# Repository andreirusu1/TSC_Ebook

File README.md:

# TSC_Ebook
Descriere Proiect
OpenBook este un proiect open source care isi propune sa creeze un e-book reader accesibil si usor de produs. Dispozitivul este conceput pentru a afisa carti digitale, oferind o experienta de lectura similara cu cea a unei carti tiparite, dar cu avantajele tehnologiei moderne. Proiectul meu se bazeaza pe o proiectare simpla si eficienta, iar in aceasta etapa s-au dezvoltat schema electronica, PCB-ul si plasarea componentelor pe placa.

Pentru a transforma aceasta viziune in realitate, am parcurs urmatoarele etape:

1)Engineering Validation (EVT): Am proiectat schema electronica si am creat PCB-ul, asigurandu-ne ca fiecare conexiune este optimizata pentru performanta si fiabilitate.

2)Modelare 3D: Am verificat plasarea componentelor pe placa intr-un mediu 3D, garantand ca designul se integreaza perfect in cadrul final al dispozitivului.

3)Partea de display, baterie si modelele 3D complete ale dispozitivului nu au fost dezvoltate inca. Acest repository se concentreaza pe proiectarea schematica, realizarea PCB-ului si plasarea componentelor pe placa in mediul 3D.

Diagrama Bloc

Mai jos se prezinta o diagrama bloc schematica a principalelor componente si a interconexiunilor acestora:

Bill Of Materials (BOM)
Nr.	Componenta	Datasheet URL	Link site pt procurare

1	ESP32-C6-WROOM-1-N8	[Datasheet](https://www.espressif.com/sites/default/files/documentation/esp32-c6-wroom-1_wroom-1u_datasheet_en.pdf)	[link](https://www.digikey.com/en/products/detail/espressif-systems/ESP32-C6-WROOM-1-N8/17728866?utm_source=snapeda&utm_campaign=buynow&utm_medium=aggregator)

2	Micro-SD	[Datasheet](https://www.attend.com.tw/data/download/file/112A-TAAR-R03_Spec.pdf)	[link](https://www.digikey.com/en/products/detail/attend-technology/112A-TAAR-R03/17633923)

3	Inductor (68µH)	[Datasheet](https://www.we-online.com/components/products/datasheet/784373170680.pdf)	[link](https://ro.mouser.com/ProductDetail/Wurth-Elektronik/784373170680?qs=sGAEpiMZZMv126LJFLh8yzGkpireax1GgDeN9GF1EUQ%3D)

4	LED	[Datasheet](https://www.bridgelux.com/sites/default/files/resource_media/DS51_Rev%20F%20Bridgelux%20SMD%203030%20Data%20sheet.pdf)	[link](https://www.digikey.com/en/products/detail/bridgelux/BXEM-27E0000-0-000/6618599)

5	Buttons	[Datasheet](https://configured-product-images.s3.amazonaws.com/Datasheets/TL3315.pdf)	[link](https://www.digikey.com/en/products/detail/e-switch/TL3315NF250Q/1870396)

6	Capacitor 	[Datasheet](https://eu.mouser.com/datasheet/2/40/cx5r_KGM-3223198.pdf)	[link](https://ro.mouser.com/ProductDetail/KYOCERA-AVX/0402YD104MAT2A?qs=4PckX6MNpMErOINbbZj3Cw%3D%3D&srsltid=AfmBOorRllqAGFDVGSlUxRe1HCu5DEMiSSNplU-KeE2woDnCuT1J4_ia)

7	Rezistori	[Datasheet](https://www.yageo.com/upload/media/product/products/datasheet/rchip/PYu-RC_Group_51_RoHS_L_12.pdf)	[link](https://www.digikey.com/en/products/detail/yageo/RC0402JR-07100KL/726416)

8	Diode (Schottky Rectifier)	[Datasheet](https://datasheets.kyocera-avx.com/schottky.pdf)	[link](https://www.digikey.com/en/products/detail/kyocera-avx/sd0805s020s1r0/3749517)

9	Connector USB (Type-C)	[Datasheet](https://gct.co/files/drawings/usb4110.pdf)	[Mouser](https://ro.mouser.com/ProductDetail/GCT/USB4110-GF-A?qs=KUoIvG%2F9IlYiZvIXQjyJeA%3D%3D&utm_id=6470900573&utm_source=google&utm_medium=cpc&utm_marketing_tactic=emeacorp&gad_source=1)

10	Test Pad 	[DataSheet](https://cdn-shop.adafruit.com/product-files/3825/3825_diagram.PDF) [link](https://componentsearchengine.com/prices/3825?manufacturer=Adafruit)

 Aceasta lista este orientativa. Componentele si specificatiile pot fi ajustate pe parcursul dezvoltarii.

Functionalitatea Hardware
Proiectul se bazeaza pe microcontroller-ul ESP32-C6, iar designul hardware a fost gandit pentru a optimiza functionalitatea si integrarea componentelor. Principalele aspecte includ:

Alimentare: Dispozitivul este alimentat printr-un regulator de tensiune care transforma 5V in 3.3V, necesar pentru functionarea corecta a ESP32-C6.

Conectivitate: ESP32-C6 pune la dispozitie mai multe interfete de comunicatie (UART, SPI, I2C), esentiale pentru conectarea senzorilor si a altor periferice.

Plasare Componentelor: Schematicul si PCB-ul au fost proiectate pentru a asigura o dispunere eficienta a componentelor, reducand interferentele electromagnetice si facilitand asamblarea manuala sau automatizata.

Verificare 3D: Modelul 3D realizat in Fusion360 (exportat ca .step) a fost folosit pentru a verifica plasarea corecta a componentelor pe placa.

Configurarea Pinilor ESP32-C6
Mai jos sunt detaliate functiile pinilor utilizati in proiect:

Pin	    Functie	          Descriere
GPIO1	  TX	            Transmiterea datelor catre periferice

GPIO3	  RX	            Receptionarea datelor de la periferice

GPIO12	I2C             SDA	Linie de date pentru comunicatia I2C

GPIO13	I2C             SCL	Linie de ceas pentru comunicatia I2C

GPIO14	Buton/Resetare	Functie de resetare a dispozitivului

Configuratia pinilor poate fi ajustata.

Planuri de Dezvoltare: Etapele urmatoare includ integrarea componentelor pentru display, alimentare prin baterie si dezvoltarea completa a modelului 3D al dispozitivului pentru validarea finala.

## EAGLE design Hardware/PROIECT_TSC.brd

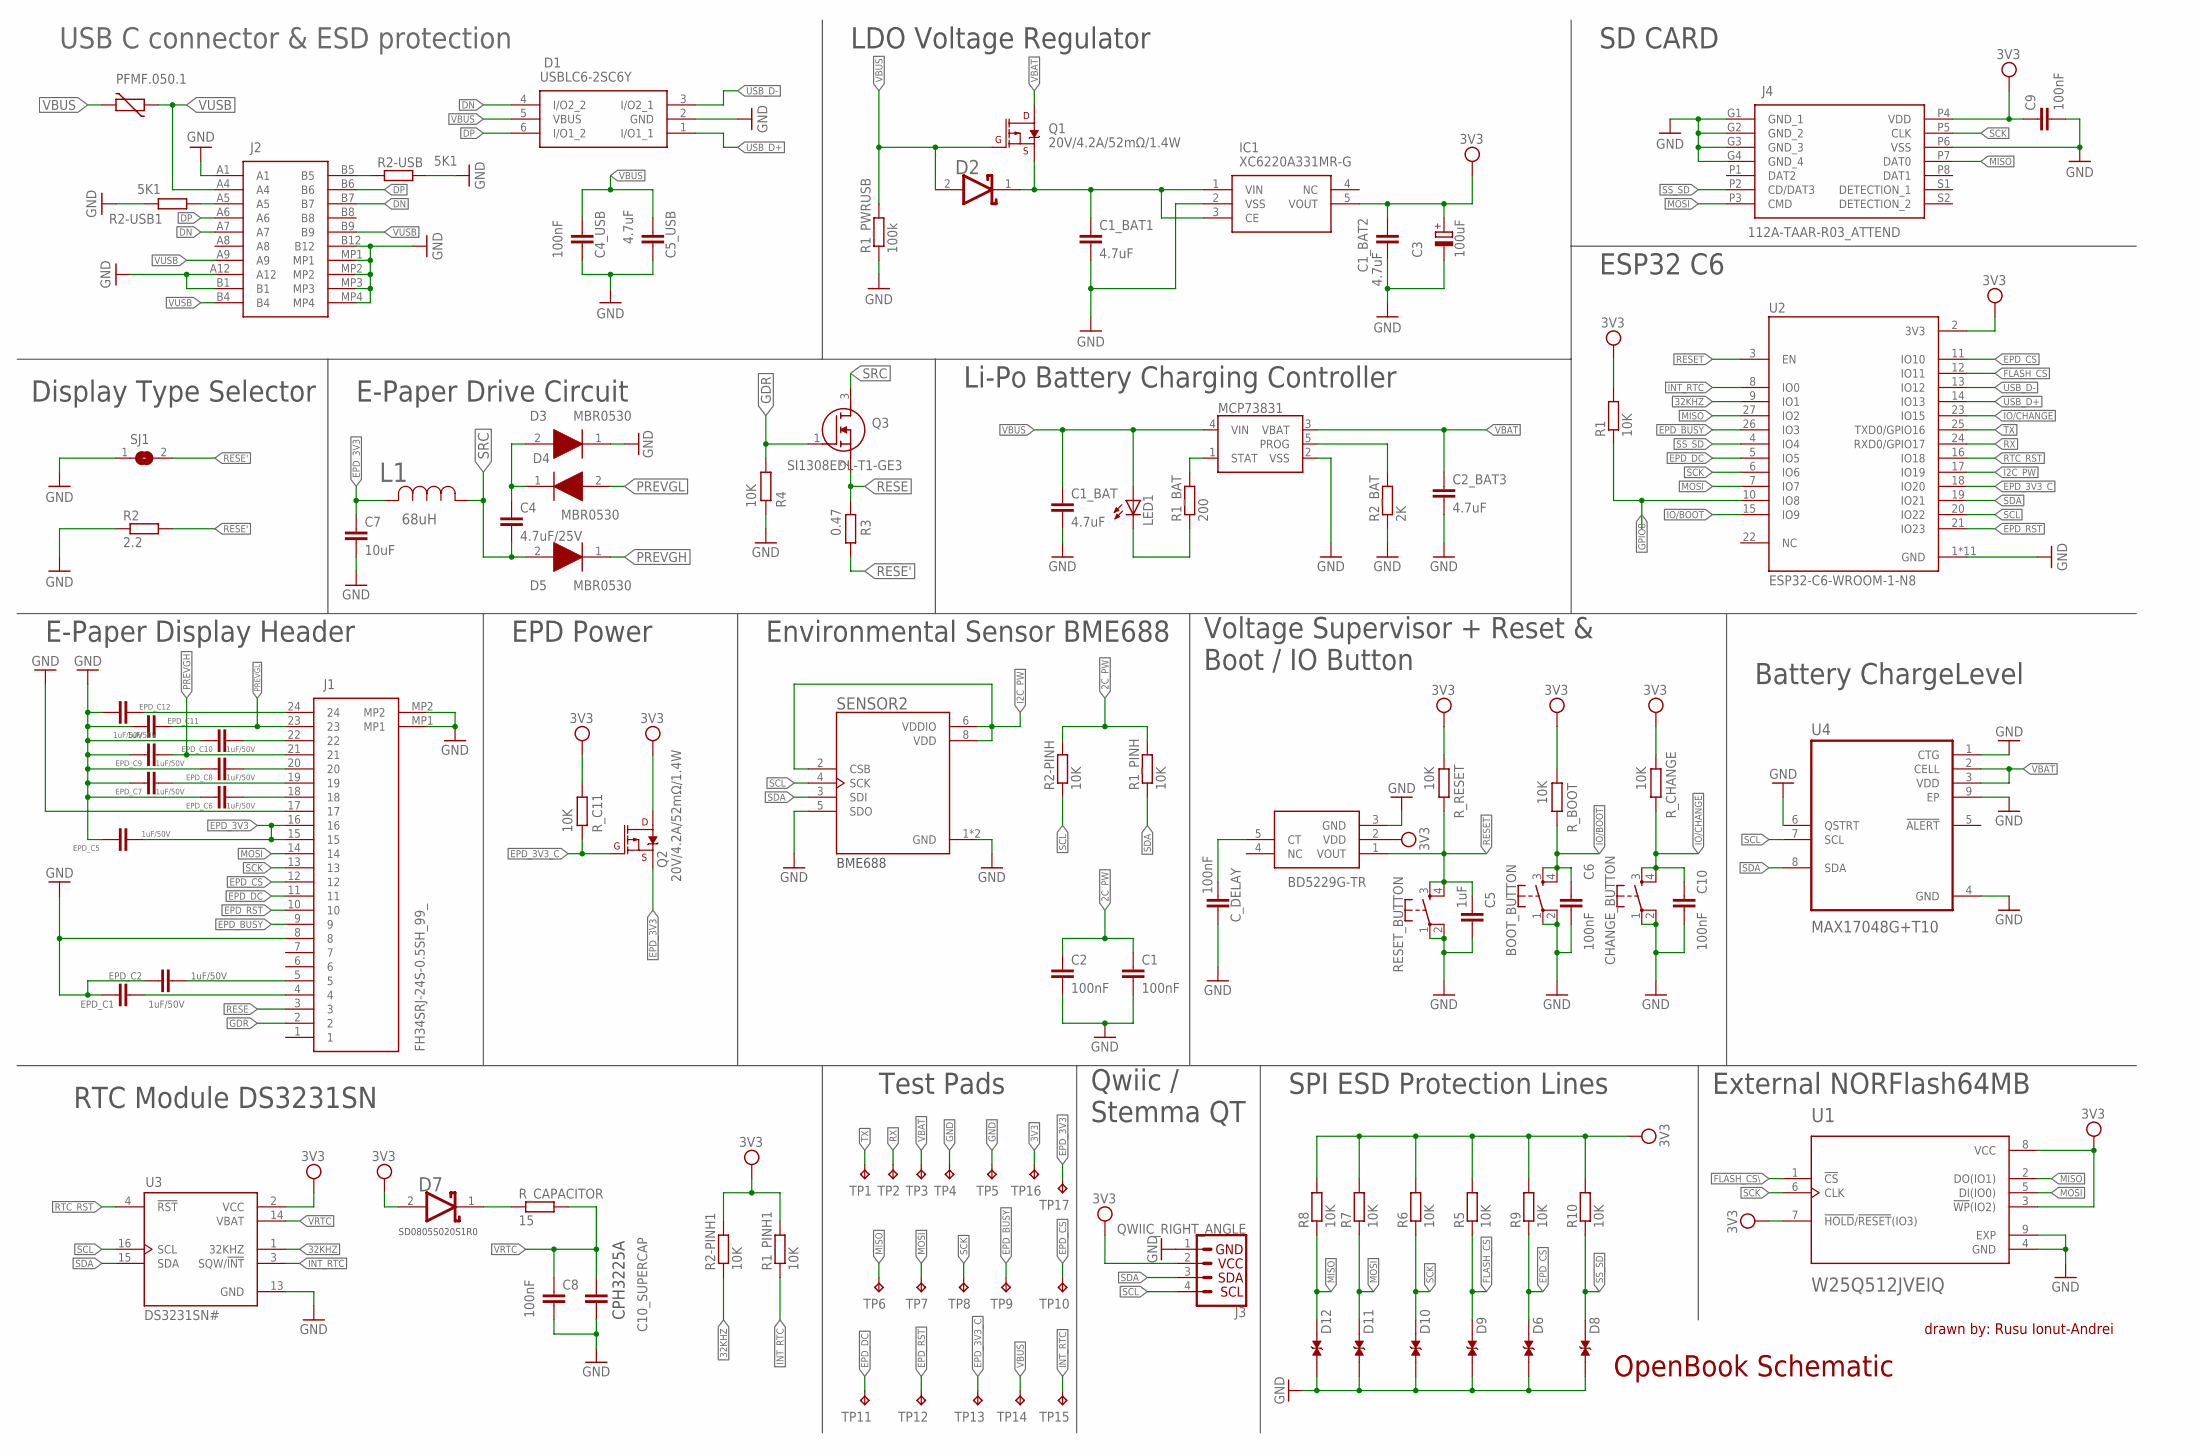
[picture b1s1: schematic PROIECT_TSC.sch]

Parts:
BOOT_BUTTON: BUTTON_CUSYOMV1; MYBUTTON
C1, C2, C6, C8, C9, C10: 100nF; ESP32_WROVER_EAGLE-LTSPICE_C0402
C1_BAT, C1_BAT1, C2_BAT3: 4.7uF; ESP32_WROVER_EAGLE-LTSPICE_C0402
C1_BAT2, C5_USB: 4.7uF; EAGLE-LTSPICE_C0402
C3: 100uF; RCL_CT3528
C4: 4.7uF/25V; ESP32_WROVER_EAGLE-LTSPICE_C0402
C4_USB: 100nF; EAGLE-LTSPICE_C0402
C5: 1uF; ESP32_WROVER_EAGLE-LTSPICE_C0402
C7: 10uF; EAGLE-LTSPICE_C0402
C10_SUPERCAP: ESP32_WROVER_EAGLE-LTSPICE_CC0402; ESP32_WROVER_EAGLE-LTSPICE_C0402
CHANGE_BUTTON: BUTTON_CUSYOMV1; MYBUTTON
C_DELAY: 100nF; ESP32_WROVER_EAGLE-LTSPICE_C0402
D1: USBLC6-2SC6Y; SOT95P280X145-6N
D2, D7: ESP32_WROVER_AVX---SD0805S020S1R0_AVX_SD0805S020S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; ESP32_WROVER_AVX---SD0805S020S1R0_AVX_SD0805S020S1R0_0
D3, D4, D5: MBR0530; SOD3716X135N
D6, D8, D9, D10, D11, D12: PGB1010603MR; DIOC1608X36N
EPD_C1, EPD_C2, EPD_C5, EPD_C6, EPD_C7, EPD_C8, EPD_C9, EPD_C10, EPD_C11, EPD_C12: 1uF/50V; ESP32_WROVER_EAGLE-LTSPICE_C0402
IC1: XC6220A331MR-G; SOT95P280X120-5N
IC2: BD5229G-TR; SOT95P280X125-5N
J1: FH34SRJ-24S-0.5SH_99_; FH34SRJ24S05SH99
J2: SAMACSYS_PARTS_USB4110-GF-A; SAMACSYS_PARTS_USB4110GFA
J3: QWIIC_RIGHT_ANGLE; JST04_1MM_RA
J4: 112A-TAAR-R03_ATTEND; 112ATAARR03ATTEND
L1: 68uH; IND_4828-WE-TPC_WRE
LED1: ADAFRUIT_LEDCHIP-LED0603; ADAFRUIT_CHIP-LED0603
MCP73831: ESP32_WROVER_SPARKFUN-IC-POWER_MCP73831; ESP32_WROVER_SPARKFUN-IC-POWER_SOT23-5
PFMF.050.1: ESP32C6_VARISTORCN1812; ESP32C6_VARISTOR_CT/CN1812
Q1, Q2: 20V/4.2A/52mΩ/1.4W; ESP32_WROVER_SPARKFUN-DISCRETESEMI_SOT23-3
Q3: SI1308EDL-T1-GE3; SOT65P210X110-3N
R1, R1_PINH, R1_PINH1, R2-PINH, R2-PINH1, R4, R5, R6, R7, R8, R9, R10: 10K; ESP32_WROVER_EAGLE-LTSPICE_R0402
R1_BAT: 200; ESP32_WROVER_EAGLE-LTSPICE_R0402
R1_PWRUSB: 100k; ESP32_WROVER_EAGLE-LTSPICE_R0402
R2: 2.2; ESP32_WROVER_EAGLE-LTSPICE_R0402
R2-USB, R2-USB1: 5K1; ESP32_WROVER_EAGLE-LTSPICE_R0402
R2_BAT: 2K; ESP32_WROVER_EAGLE-LTSPICE_R0402
R3: 0.47; ESP32_WROVER_EAGLE-LTSPICE_R0402
RESET_BUTTON: BUTTON_CUSYOMV1; MYBUTTON
R_BOOT: 10K; ESP32_WROVER_EAGLE-LTSPICE_R0402
R_C11: 10K; ESP32_WROVER_EAGLE-LTSPICE_R0402
R_CAPACITOR: 15; ESP32_WROVER_EAGLE-LTSPICE_R0402
R_CHANGE: 10K; ESP32_WROVER_EAGLE-LTSPICE_R0402
R_RESET: 10K; ESP32_WROVER_EAGLE-LTSPICE_R0402
SENSOR2: ESP32_WROVER_BME680_BME680; ESP32_WROVER_BME680_PSON80P300X300X100-8N
SJ1: SJ
TP1, TP2, TP3, TP4, TP5, TP6, TP7, TP8, TP9, TP10, TP11, TP12, TP13, TP14, TP15, TP16, TP17: TPTP20R; TP20R
U1: W25Q512JVEIQ; SON127P600X800X80-9N
U2: ESP32-C6-WROOM-1-N8; XCVR_ESP32-C6-WROOM-1-N8
U3: DS3231SN#; SOIC127P1032X265-16N
U4: MAX17048G+T10; SON50P200X200X80-9N

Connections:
2C_PW: C1.1, C2.1, R1_PINH.2, R2-PINH.2
3V3: C1_BAT2.1, C3.+, C9.1, D7.2 (ANODE), IC1.5 (VOUT), IC2.2 (VDD), J3.2, J4.P4 (VDD), Q2.3 (D), R1.2, R1_PINH1.2, R2-PINH1.2, R5.2, R6.2, R7.2, R8.2, R9.2, R10.2, R_BOOT.2, R_C11.2, R_CHANGE.2, R_RESET.2, TP16.TP, U1.3 (!WP!(IO2)), U1.7 (!HOLD!/!RESET!(IO3)), U1.8 (VCC), U2.2 (3V3), U3.2 (VCC)
32KHZ: R2-PINH1.1, U2.9 (IO1), U3.1 (32KHZ)
DN: D1.4 (I/O2_2), J2.A7, J2.B7
DP: D1.6 (I/O1_2), J2.A6, J2.B6
EPD_3V3: C7.1, EPD_C5.2, J1.15, J1.16, L1.2, Q2.2 (S), TP17.TP
EPD_3V3_C: Q2.1 (G), R_C11.1, TP13.TP, U2.18 (IO20)
EPD_BUSY: J1.9, TP9.TP, U2.26 (IO3)
EPD_CS: D6.2, J1.12, R9.1, TP10.TP, U2.11 (IO10)
EPD_DC: J1.11, TP11.TP, U2.5 (IO5)
EPD_RST: J1.10, TP12.TP, U2.21 (IO23)
FLASH_CS: D9.2, R5.1, U2.12 (IO11)
FLASH_CS\: U1.1 (!CS)
GDR: J1.2, Q3.1 (G), R4.2
GND: BOOT_BUTTON.1, BOOT_BUTTON.2, C1.2, C1_BAT.2, C1_BAT1.2, C1_BAT2.2, C2.2, C2_BAT3.2, C3.-, C4_USB.2, C5.2, C5_USB.2, C6.2, C7.2, C8.2, C9.2, C10.2, C10_SUPERCAP.2, CHANGE_BUTTON.1, CHANGE_BUTTON.2, C_DELAY.2, D1.2 (GND), D3.1 (K), D6.1, D8.1, D9.1, D10.1, D11.1, D12.1, EPD_C1.1, EPD_C2.1, EPD_C5.1, EPD_C6.1, EPD_C7.1, EPD_C8.1, EPD_C9.1, EPD_C10.1, EPD_C11.1, EPD_C12.1, IC1.2 (VSS), IC2.3 (GND), J1.8, J1.17, J1.MP1, J1.MP2, J2.A1, J2.A12, J2.B1, J2.B12, J2.MP1, J2.MP2, J2.MP3, J2.MP4, J3.1, J4.G1 (GND_1), J4.G2 (GND_2), J4.G3 (GND_3), J4.G4 (GND_4), J4.P6 (VSS), MCP73831.2 (VSS), R1_PWRUSB.1, R2.1, R2-USB.2, R2-USB1.1, R2_BAT.1, R4.1, RESET_BUTTON.1, RESET_BUTTON.2, SENSOR2.1 (GND), SENSOR2.5 (SDO), SENSOR2.7 (GND), SJ1.1, TP4.TP, TP5.TP, U1.4 (GND), U1.9 (EXP), U2.1 (GND), U2.28 (GND), U2.29_1 (GND), U2.29_2 (GND), U2.29_3 (GND), U2.29_4 (GND), U2.29_5 (GND), U2.29_6 (GND), U2.29_7 (GND), U2.29_8 (GND), U2.29_9 (GND), U3.13 (GND), U4.1 (CTG), U4.4 (GND), U4.6 (QSTRT), U4.9 (EP)
GPIO8: R1.1, U2.10 (IO8)
I2C_PW: SENSOR2.2 (CSB), SENSOR2.6 (VDDIO), SENSOR2.8 (VDD), U2.17 (IO19)
INT_RTC: R1_PINH1.1, TP15.TP, U2.8 (IO0), U3.3 (SQW/!INT)
IO/BOOT: BOOT_BUTTON.3, BOOT_BUTTON.4, C6.1, R_BOOT.1, U2.15 (IO9)
IO/CHANGE: C10.1, CHANGE_BUTTON.3, CHANGE_BUTTON.4, R_CHANGE.1, U2.23 (IO15)
MISO: D12.2, J4.P7 (DAT0), R8.1, TP6.TP, U1.2 (DO(IO1)), U2.27 (IO2)
MOSI: D11.2, J1.14, J4.P3 (CMD), R7.1, TP7.TP, U1.5 (DI(IO0)), U2.7 (IO7)
unnamed: C1_BAT1.1, D2.1 (CATHODE), IC1.1 (VIN), IC1.3 (CE), Q1.2 (S)
unnamed: J2.A5, R2-USB1.2
unnamed: C4.1, D3.2 (A), D4.1 (K)
unnamed: J2.B5, R2-USB.1
unnamed: MCP73831.1 (STAT), R1_BAT.2
unnamed: MCP73831.5 (PROG), R2_BAT.2
unnamed: LED1.C, R1_BAT.1
unnamed: EPD_C12.2, J1.24
unnamed: EPD_C2.2, J1.5
unnamed: EPD_C1.2, J1.4
unnamed: EPD_C6.2, J1.18
unnamed: EPD_C10.2, J1.22
unnamed: EPD_C8.2, J1.20
unnamed: D7.1 (CATHODE), R_CAPACITOR.1
unnamed: EPD_C7.2, J1.19
unnamed: C_DELAY.1, IC2.5 (CT)
PREVGH: D5.1 (K), EPD_C9.2, J1.21
PREVGL: D4.2 (A), EPD_C11.2, J1.23
RESE: J1.3, Q3.2 (S), R3.2
RESE': R2.2, R3.1, SJ1.2
RESET: C5.1, IC2.1 (VOUT), RESET_BUTTON.3, RESET_BUTTON.4, R_RESET.1, U2.3 (EN)
RTC_RST: U2.16 (IO18), U3.4 (!RST)
RX: TP2.TP, U2.24 (RXD0/GPIO17)
SCK: D10.2, J1.13, J4.P5 (CLK), R6.1, TP8.TP, U1.6 (CLK), U2.6 (IO6)
SCL: J3.4, R2-PINH.1, SENSOR2.4 (SCK), U2.20 (IO22), U3.16 (SCL), U4.7 (SCL)
SDA: J3.3, R1_PINH.1, SENSOR2.3 (SDI), U2.19 (IO21), U3.15 (SDA), U4.8 (SDA)
SRC: C4.2, D5.2 (A), L1.1, Q3.3 (D)
SS_SD: D8.2, J4.P2 (CD/DAT3), R10.1, U2.4 (IO4)
TX: TP1.TP, U2.25 (TXD0/GPIO16)
USB_D+: D1.1 (I/O1_1), U2.14 (IO13)
USB_D-: D1.3 (I/O2_1), U2.13 (IO12)
VBAT: C2_BAT3.1, MCP73831.3 (VBAT), Q1.3 (D), TP3.TP, U4.2 (CELL), U4.3 (VDD)
VBUS: C1_BAT.1, C4_USB.1, C5_USB.1, D1.5 (VBUS), D2.2 (ANODE), LED1.A, MCP73831.4 (VIN), PFMF.050.1.2, Q1.1 (G), R1_PWRUSB.2, TP14.TP
VRTC: C8.1, C10_SUPERCAP.1, R_CAPACITOR.2, U3.14 (VBAT)
VUSB: J2.A4, J2.A9, J2.B4, J2.B9, PFMF.050.1.1

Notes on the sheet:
USB C connector & ESD protection
LDO Voltage Regulator
SD CARD
Display Type Selector
E-Paper Drive Circuit
ESP32 C6
Li-Po Battery Charging Controller
E-Paper Display Header
EPD Power
Environmental Sensor BME688
BME688
Battery ChargeLevel
Voltage Supervisor + Reset & Boot / IO Button
OpenBook Schematic
drawn by: Rusu Ionut-Andrei
External NORFlash64MB
SPI ESD Protection Lines
Qwiic / Stemma QT
Test Pads
RTC Module DS3231SN
CPH3225A
SD0805S020S1R0

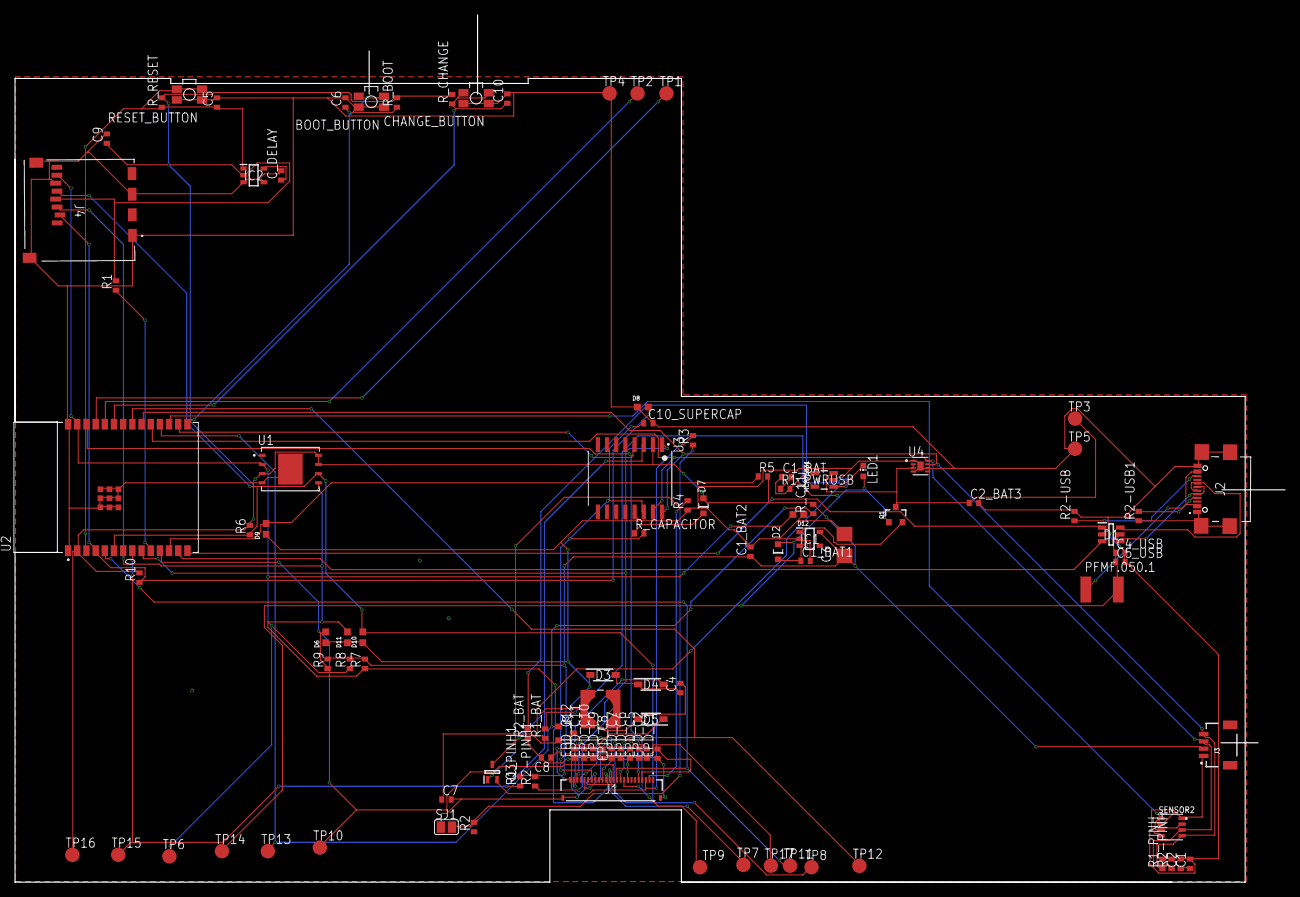
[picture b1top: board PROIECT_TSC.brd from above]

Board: 2 copper layers, 175.7 x 120.0 mm, 103 parts (0 on the bottom side), 56 nets.

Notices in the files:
parts and their libraries:
COPYRIGHT: Copyright (C) 2024 Ultra Librarian. All rights reserved.
